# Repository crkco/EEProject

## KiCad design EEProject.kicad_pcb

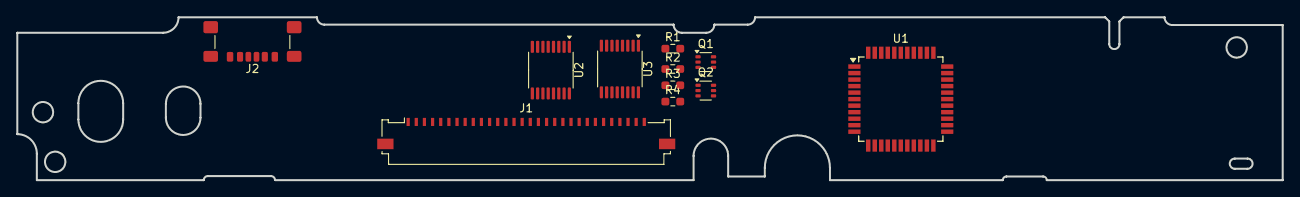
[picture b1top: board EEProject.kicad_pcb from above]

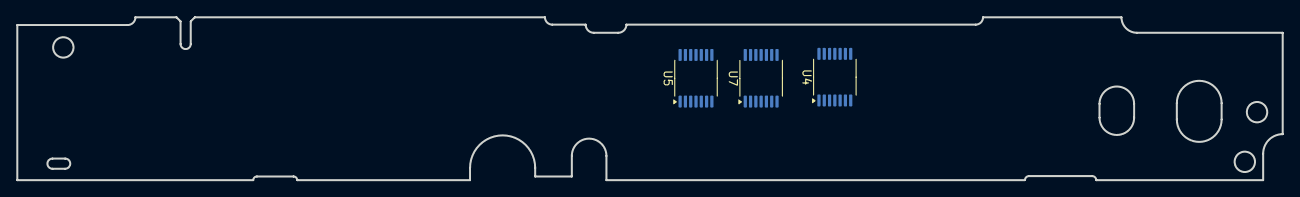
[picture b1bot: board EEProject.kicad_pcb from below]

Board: 2 copper layers, 155.4 x 20.0 mm, 14 parts (3 on the bottom side), 45 nets, no tracks yet.

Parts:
J1: Flex_Cable_Connector_1.0_1x30; Molex_200528-0300_1x30-1MP_P1.00mm_Horizontal
J2: USB_C_Receptacle_USB2.0_14P; USB_C_Receptacle_GCT_USB4135-GF-A_6P_TopMnt_Horizontal
Q1, Q2: PUMX1; SOT-363_SC-70-6
R1, R2, R3, R4: R; R_0603_1608Metric_Pad0.98x0.95mm_HandSolder
U1: ATmega32U4-A; TQFP-44_10x10mm_P0.8mm
U2, U3: 74HC595; TSSOP-16_4.4x5mm_P0.65mm
U4, U5, U7: VC07A; TSSOP-14_4.4x5mm_P0.65mm

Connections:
GND: J2.A12 (GND), J2.B12 (GND), R1.2, R2.2, R3.2, R4.2
unnamed: J1.1, U7.8 (4Y)
unnamed: J1.2, U7.6 (3Y)
unnamed: J1.3, U7.4 (2Y)
unnamed: J1.4, U7.2 (1Y)
unnamed: J1.5, U5.12 (6Y)
unnamed: J1.6, U5.10 (5Y)
unnamed: J1.7, U5.8 (4Y)
unnamed: J1.8, U5.6 (3Y)
unnamed: J1.9, U5.4 (2Y)
unnamed: J1.10, U5.2 (1Y)
unnamed: J1.11, U4.12 (6Y)
unnamed: J1.12, U4.10 (5Y)
unnamed: J1.13, U4.8 (4Y)
unnamed: J1.14, U4.6 (3Y)
unnamed: J1.15, U4.4 (2Y)
unnamed: J1.16, U4.2 (1Y)
unnamed: J1.27, Q2.3 (C2)
unnamed: J1.28, Q2.6 (C1)
unnamed: J1.29, Q1.3 (C2)
unnamed: J1.30, Q1.6 (C1)
unnamed: Q1.1 (E1), R1.1
unnamed: Q1.4 (E2), R2.1
unnamed: Q2.1 (E1), R3.1
unnamed: Q2.4 (E2), R4.1
unnamed: J2.A9 (VBUS), J2.B9 (VBUS)
unnamed: U1.24 (AVCC), U1.44 (AVCC)
unnamed: U1.15 (GND), U1.23 (GND), U1.35 (GND), U1.43 (GND)
unnamed: U2.15 (QA), U4.1 (1A)
unnamed: U2.1 (QB), U4.3 (2A)
unnamed: U2.2 (QC), U4.5 (3A)
unnamed: U2.3 (QD), U4.9 (4A)
unnamed: U2.4 (QE), U4.11 (5A)
unnamed: U2.5 (QF), U4.13 (6A)
unnamed: U2.6 (QG), U5.1 (1A)
unnamed: U2.7 (QH), U5.3 (2A)
unnamed: U3.15 (QA), U5.5 (3A)
unnamed: U3.1 (QB), U5.9 (4A)
unnamed: U3.2 (QC), U5.11 (5A)
unnamed: U3.3 (QD), U5.13 (6A)
unnamed: U3.4 (QE), U7.1 (1A)
unnamed: U3.5 (QF), U7.3 (2A)
unnamed: U3.6 (QG), U7.5 (3A)
unnamed: U3.7 (QH), U7.9 (4A)
VCC: U1.14 (VCC), U1.34 (VCC)

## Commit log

2024-10-03 test
2024-10-03 Devided schmetic into sub parts + ICs
2024-10-03 Added base PCB + base schematics
2024-10-03 test check
2024-10-03 Seperated Schematics
2024-10-03 Keyboard Data Changes and added footprints
2024-10-05 Atmega34u4
2024-10-10 UART passive components
2024-11-10 11.10.2024
